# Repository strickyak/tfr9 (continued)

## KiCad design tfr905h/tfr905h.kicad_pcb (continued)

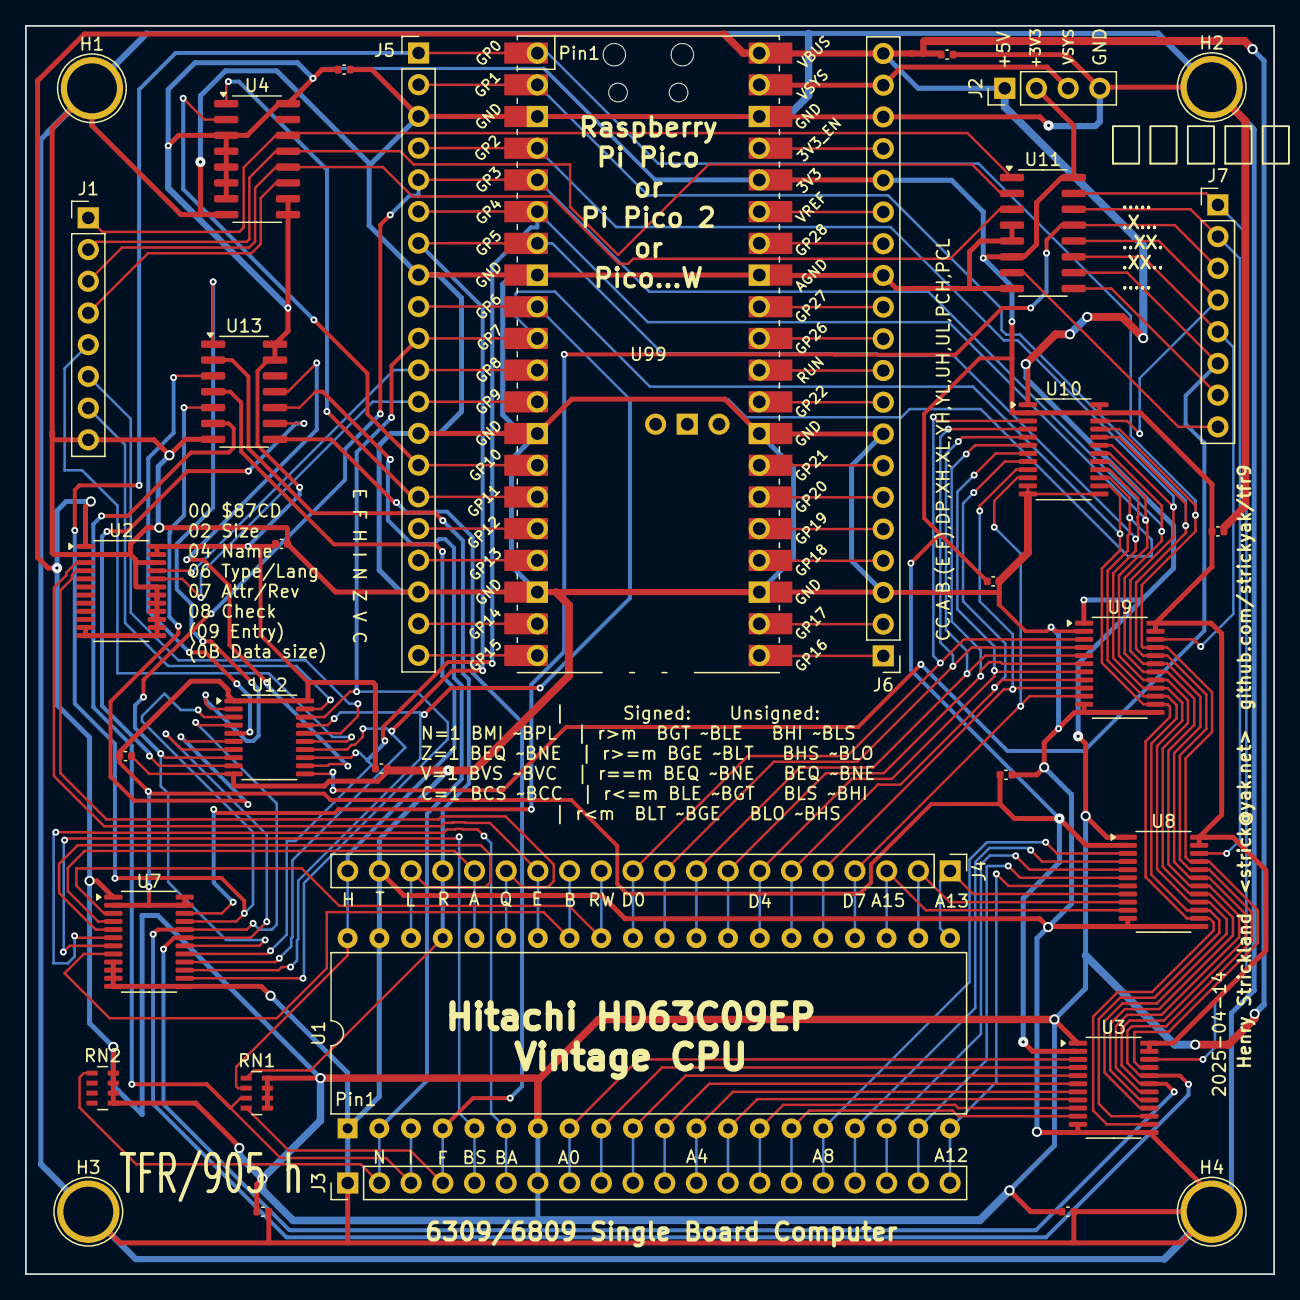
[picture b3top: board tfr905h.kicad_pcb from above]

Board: 2 copper layers, 100.0 x 100.0 mm, 35 parts (0 on the bottom side), 90 nets.

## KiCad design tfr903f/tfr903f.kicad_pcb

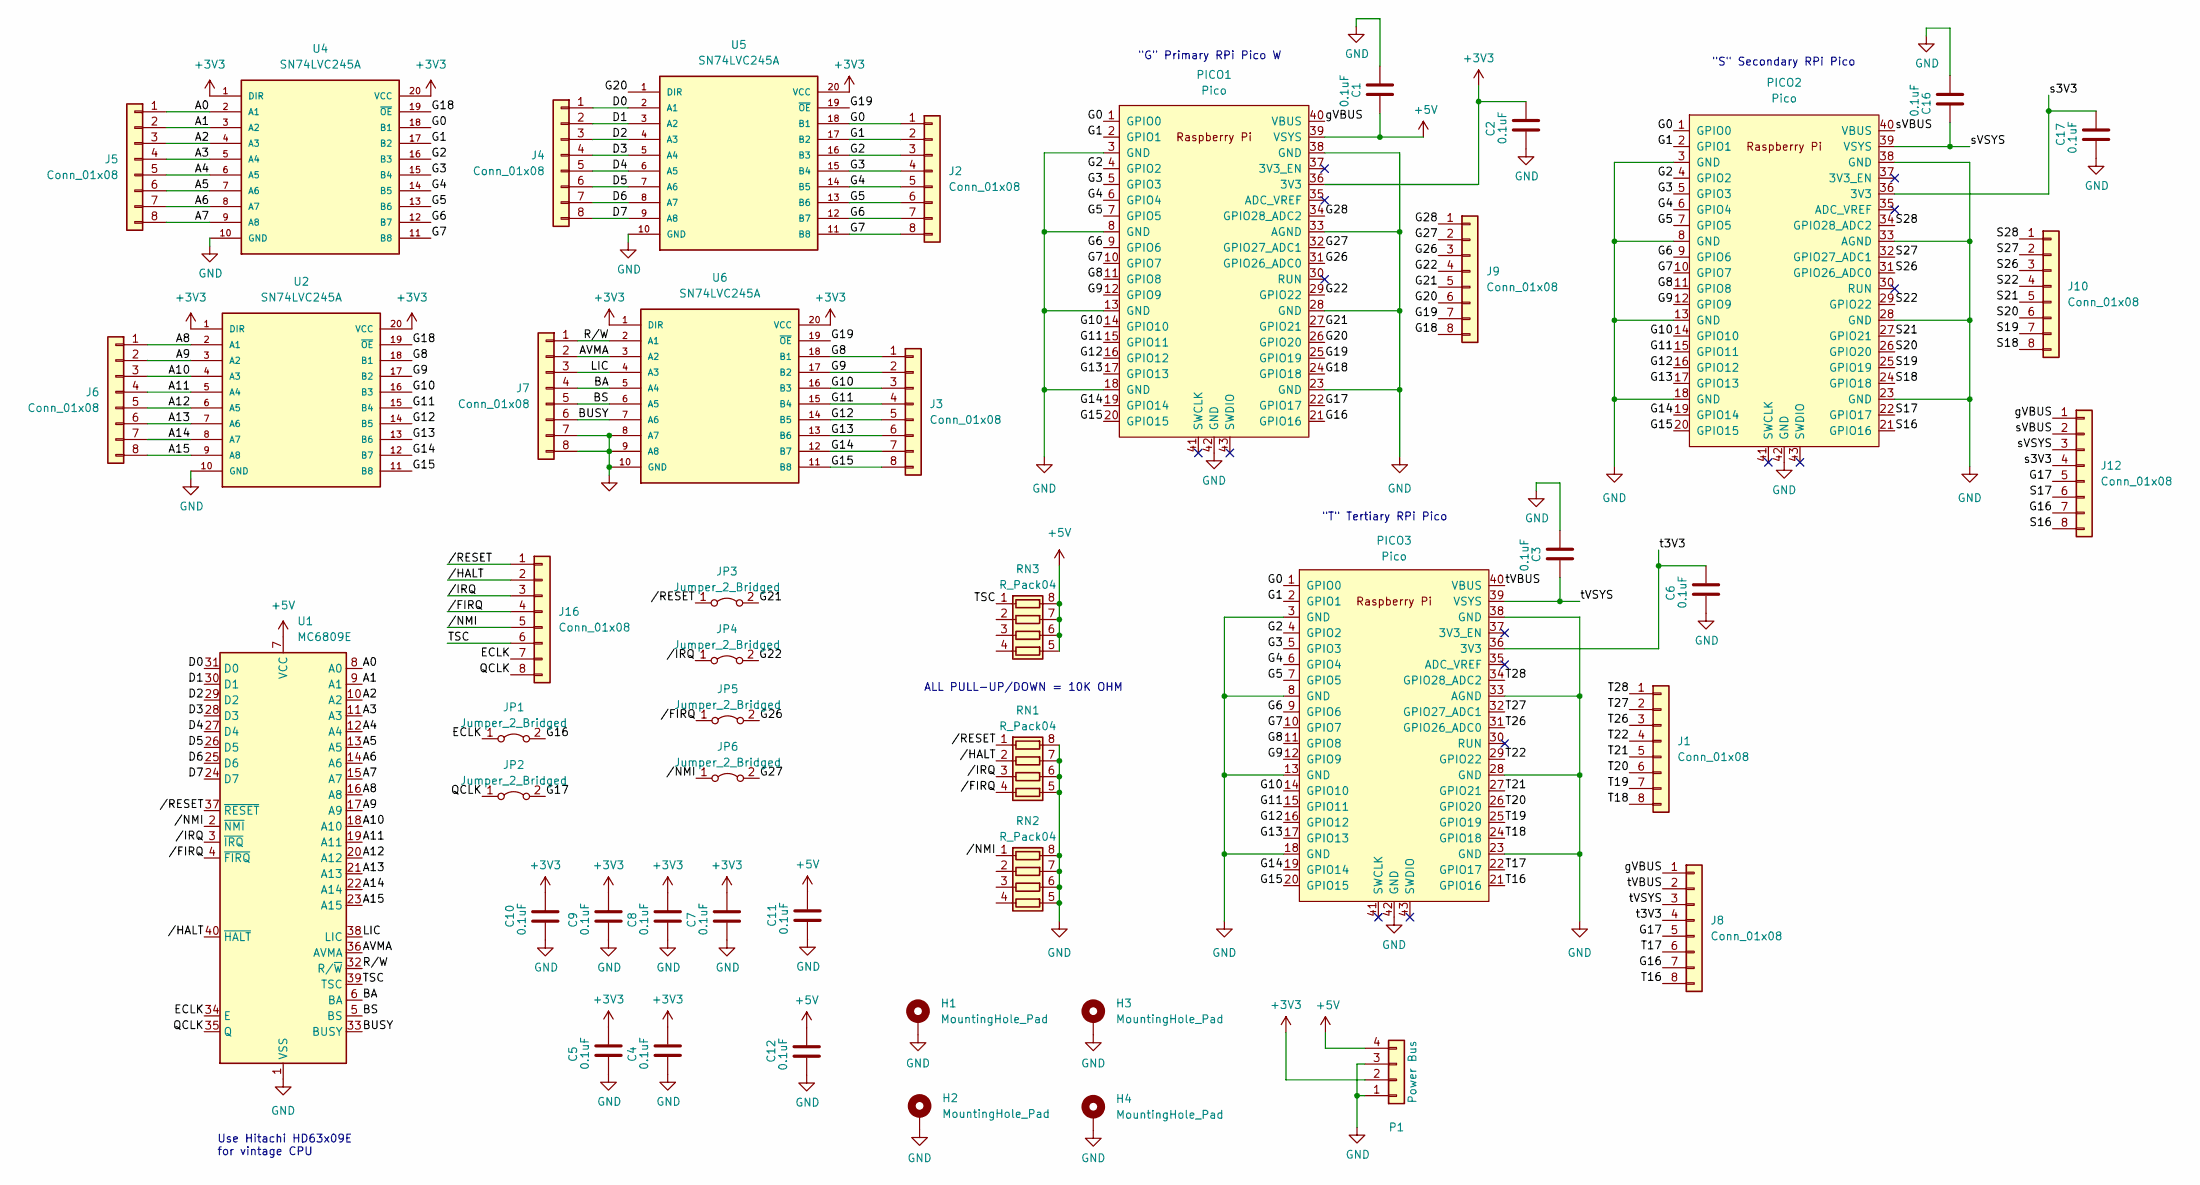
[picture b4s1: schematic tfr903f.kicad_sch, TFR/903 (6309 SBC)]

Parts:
C1, C2, C3, C4, C5, C6, C7, C8, C9, C10, C11, C12, C16, C17: 0.1uF; C_0402_1005Metric
H1, H2, H3, H4: MountingHole_Pad; TestPoint_Plated_Hole_D4.0mm
J1, J2, J3, J4, J5, J6, J7, J8, J9, J10, J12, J16: Conn_01x08; PinHeader_1x08_P2.54mm_Vertical
JP1, JP2, JP3, JP4, JP5, JP6: Jumper_2_Bridged; SolderJumper-2_P1.3mm_Bridged_Pad1.0x1.5mm
P1: Power Bus; PinHeader_1x04_P2.54mm_Vertical
PICO1, PICO2, PICO3: Pico; RPi_PicoW_SMD_TH
RN1, RN2, RN3: R_Pack04; R_Array_Concave_4x0603
U1: MC6809E; DIP-40_W15.24mm
U2, U4, U5, U6: SN74LVC245A; TSSOP-20_4.4x6.5mm_P0.65mm; MPN SN74LVC245AN

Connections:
+3V3: C2.1, C4.1, C5.1, C7.1, C8.1, C9.1, C10.1, P1.2, PICO1.36 (3V3), U2.1 (DIR), U2.20 (VCC), U4.1 (DIR), U4.20 (VCC), U5.20 (VCC), U6.1 (DIR), U6.20 (VCC)
+5V: C1.1, C11.1, C12.1, P1.4, PICO1.39 (VSYS), RN3.5 (R4.2), RN3.6 (R3.2), RN3.7 (R2.2), RN3.8 (R1.2), U1.7 (VCC)
/A0: J5.1, U1.8 (A0), U4.2 (A1)
/A1: J5.2, U1.9 (A1), U4.3 (A2)
/A2: J5.3, U1.10 (A2), U4.4 (A3)
/A3: J5.4, U1.11 (A3), U4.5 (A4)
/A4: J5.5, U1.12 (A4), U4.6 (A5)
/A5: J5.6, U1.13 (A5), U4.7 (A6)
/A6: J5.7, U1.14 (A6), U4.8 (A7)
/A7: J5.8, U1.15 (A7), U4.9 (A8)
/A8: J6.1, U1.16 (A8), U2.2 (A1)
/A9: J6.2, U1.17 (A9), U2.3 (A2)
/A10: J6.3, U1.18 (A10), U2.4 (A3)
/A11: J6.4, U1.19 (A11), U2.5 (A4)
/A12: J6.5, U1.20 (A12), U2.6 (A5)
/A13: J6.6, U1.21 (A13), U2.7 (A6)
/A14: J6.7, U1.22 (A14), U2.8 (A7)
/A15: J6.8, U1.23 (A15), U2.9 (A8)
/AVMA: J7.2, U1.36 (AVMA), U6.3 (A2)
/BA: J7.4, U1.6 (BA), U6.5 (A4)
/BS: J7.5, U1.5 (BS), U6.6 (A5)
/BUSY: J7.6, U1.33 (BUSY), U6.7 (A6)
/D0: J4.1, U1.31 (D0), U5.2 (A1)
/D1: J4.2, U1.30 (D1), U5.3 (A2)
/D2: J4.3, U1.29 (D2), U5.4 (A3)
/D3: J4.4, U1.28 (D3), U5.5 (A4)
/D4: J4.5, U1.27 (D4), U5.6 (A5)
/D5: J4.6, U1.26 (D5), U5.7 (A6)
/D6: J4.7, U1.25 (D6), U5.8 (A7)
/D7: J4.8, U1.24 (D7), U5.9 (A8)
/ECLK: J16.7, JP1.1 (A), U1.34 (E)
/G0: J2.1, PICO1.1 (GPIO0), PICO2.1 (GPIO0), PICO3.1 (GPIO0), U4.18 (B1), U5.18 (B1)
/G1: J2.2, PICO1.2 (GPIO1), PICO2.2 (GPIO1), PICO3.2 (GPIO1), U4.17 (B2), U5.17 (B2)
/G2: J2.3, PICO1.4 (GPIO2), PICO2.4 (GPIO2), PICO3.4 (GPIO2), U4.16 (B3), U5.16 (B3)
/G3: J2.4, PICO1.5 (GPIO3), PICO2.5 (GPIO3), PICO3.5 (GPIO3), U4.15 (B4), U5.15 (B4)
/G4: J2.5, PICO1.6 (GPIO4), PICO2.6 (GPIO4), PICO3.6 (GPIO4), U4.14 (B5), U5.14 (B5)
/G5: J2.6, PICO1.7 (GPIO5), PICO2.7 (GPIO5), PICO3.7 (GPIO5), U4.13 (B6), U5.13 (B6)
/G6: J2.7, PICO1.9 (GPIO6), PICO2.9 (GPIO6), PICO3.9 (GPIO6), U4.12 (B7), U5.12 (B7)
/G7: J2.8, PICO1.10 (GPIO7), PICO2.10 (GPIO7), PICO3.10 (GPIO7), U4.11 (B8), U5.11 (B8)
/G8: J3.1, PICO1.11 (GPIO8), PICO2.11 (GPIO8), PICO3.11 (GPIO8), U2.18 (B1), U6.18 (B1)
/G9: J3.2, PICO1.12 (GPIO9), PICO2.12 (GPIO9), PICO3.12 (GPIO9), U2.17 (B2), U6.17 (B2)
/G10: J3.3, PICO1.14 (GPIO10), PICO2.14 (GPIO10), PICO3.14 (GPIO10), U2.16 (B3), U6.16 (B3)
/G11: J3.4, PICO1.15 (GPIO11), PICO2.15 (GPIO11), PICO3.15 (GPIO11), U2.15 (B4), U6.15 (B4)
/G12: J3.5, PICO1.16 (GPIO12), PICO2.16 (GPIO12), PICO3.16 (GPIO12), U2.14 (B5), U6.14 (B5)
/G13: J3.6, PICO1.17 (GPIO13), PICO2.17 (GPIO13), PICO3.17 (GPIO13), U2.13 (B6), U6.13 (B6)
/G14: J3.7, PICO1.19 (GPIO14), PICO2.19 (GPIO14), PICO3.19 (GPIO14), U2.12 (B7), U6.12 (B7)
/G15: J3.8, PICO1.20 (GPIO15), PICO2.20 (GPIO15), PICO3.20 (GPIO15), U2.11 (B8), U6.11 (B8)
/G16: J8.7, J12.7, JP1.2 (B), PICO1.21 (GPIO16)
/G17: J8.5, J12.5, JP2.2 (B), PICO1.22 (GPIO17)
/G18: J9.8, PICO1.24 (GPIO18), U2.19 (~OE), U4.19 (~OE)
/G19: J9.7, PICO1.25 (GPIO19), U5.19 (~OE), U6.19 (~OE)
/G20: J9.6, PICO1.26 (GPIO20), U5.1 (DIR)
/G21: J9.5, JP3.2 (B), PICO1.27 (GPIO21)
/G22: J9.4, JP4.2 (B), PICO1.29 (GPIO22)
/G26: J9.3, JP5.2 (B), PICO1.31 (GPIO26_ADC0)
/G27: J9.2, JP6.2 (B), PICO1.32 (GPIO27_ADC1)
/G28: J9.1, PICO1.34 (GPIO28_ADC2)
/LIC: J7.3, U1.38 (LIC), U6.4 (A3)
/QCLK: J16.8, JP2.1 (A), U1.35 (Q)
/R/W: J7.1, U1.32 (R/~W), U6.2 (A1)
/S16: J12.8, PICO2.21 (GPIO16)
/S17: J12.6, PICO2.22 (GPIO17)
/S18: J10.8, PICO2.24 (GPIO18)
/S19: J10.7, PICO2.25 (GPIO19)
/S20: J10.6, PICO2.26 (GPIO20)
/S21: J10.5, PICO2.27 (GPIO21)
/S22: J10.4, PICO2.29 (GPIO22)
/S26: J10.3, PICO2.31 (GPIO26_ADC0)
/S27: J10.2, PICO2.32 (GPIO27_ADC1)
/S28: J10.1, PICO2.34 (GPIO28_ADC2)
/T16: J8.8, PICO3.21 (GPIO16)
/T17: J8.6, PICO3.22 (GPIO17)
/T18: J1.8, PICO3.24 (GPIO18)
/T19: J1.7, PICO3.25 (GPIO19)
/T20: J1.6, PICO3.26 (GPIO20)
/T21: J1.5, PICO3.27 (GPIO21)
/T22: J1.4, PICO3.29 (GPIO22)
/T26: J1.3, PICO3.31 (GPIO26_ADC0)
/T27: J1.2, PICO3.32 (GPIO27_ADC1)
/T28: J1.1, PICO3.34 (GPIO28_ADC2)
/TSC: J16.6, RN3.1 (R1.1), U1.39 (TSC)
/gVBUS: J8.1, J12.1, PICO1.40 (VBUS)
/s3V3: C17.1, J12.4, PICO2.36 (3V3)
/sVBUS: J12.2, PICO2.40 (VBUS)
/sVSYS: C16.1, J12.3, PICO2.39 (VSYS)
/t3V3: C6.1, J8.4, PICO3.36 (3V3)
/tVBUS: J8.2, PICO3.40 (VBUS)
/tVSYS: C3.1, J8.3, PICO3.39 (VSYS)
//FIRQ: J16.4, JP5.1 (A), RN1.4 (R4.1), U1.4 (~FIRQ)
//HALT: J16.2, RN1.2 (R2.1), U1.40 (~HALT)
//IRQ: J16.3, JP4.1 (A), RN1.3 (R3.1), U1.3 (~IRQ)
//NMI: J16.5, JP6.1 (A), RN2.1 (R1.1), U1.2 (~NMI)
//RESET: J16.1, JP3.1 (A), RN1.1 (R1.1), U1.37 (~RESET)
GND: C1.2, C2.2, C3.2, C4.2, C5.2, C6.2, C7.2, C8.2, C9.2, C10.2, C11.2, C12.2, C16.2, C17.2, H1.1, H2.1, H3.1, H4.1, J7.7, J7.8, P1.1, P1.3, PICO1.3 (GND), PICO1.8 (GND), PICO1.13 (GND), PICO1.18 (GND), PICO1.23 (GND), PICO1.28 (GND), PICO1.33 (AGND), PICO1.38 (GND), PICO1.42 (GND), PICO2.3 (GND), PICO2.8 (GND), PICO2.13 (GND), PICO2.18 (GND), PICO2.23 (GND), PICO2.28 (GND), PICO2.33 (AGND), PICO2.38 (GND), PICO2.42 (GND), PICO3.3 (GND), PICO3.8 (GND), PICO3.13 (GND), PICO3.18 (GND), PICO3.23 (GND), PICO3.28 (GND), PICO3.33 (AGND), PICO3.38 (GND), PICO3.42 (GND), RN1.5 (R4.2), RN1.6 (R3.2), RN1.7 (R2.2), RN1.8 (R1.2), RN2.5 (R4.2), RN2.6 (R3.2), RN2.7 (R2.2), RN2.8 (R1.2), U1.1 (VSS), U2.10 (GND), U4.10 (GND), U5.10 (GND), U6.8 (A7), U6.9 (A8), U6.10 (GND)

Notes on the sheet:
"G" Primary RPi Pico W
"T" Tertiary RPi Pico
"S" Secondary RPi Pico
ALL PULL-UP/DOWN = 10K OHM
Use Hitachi HD63x09E for vintage CPU

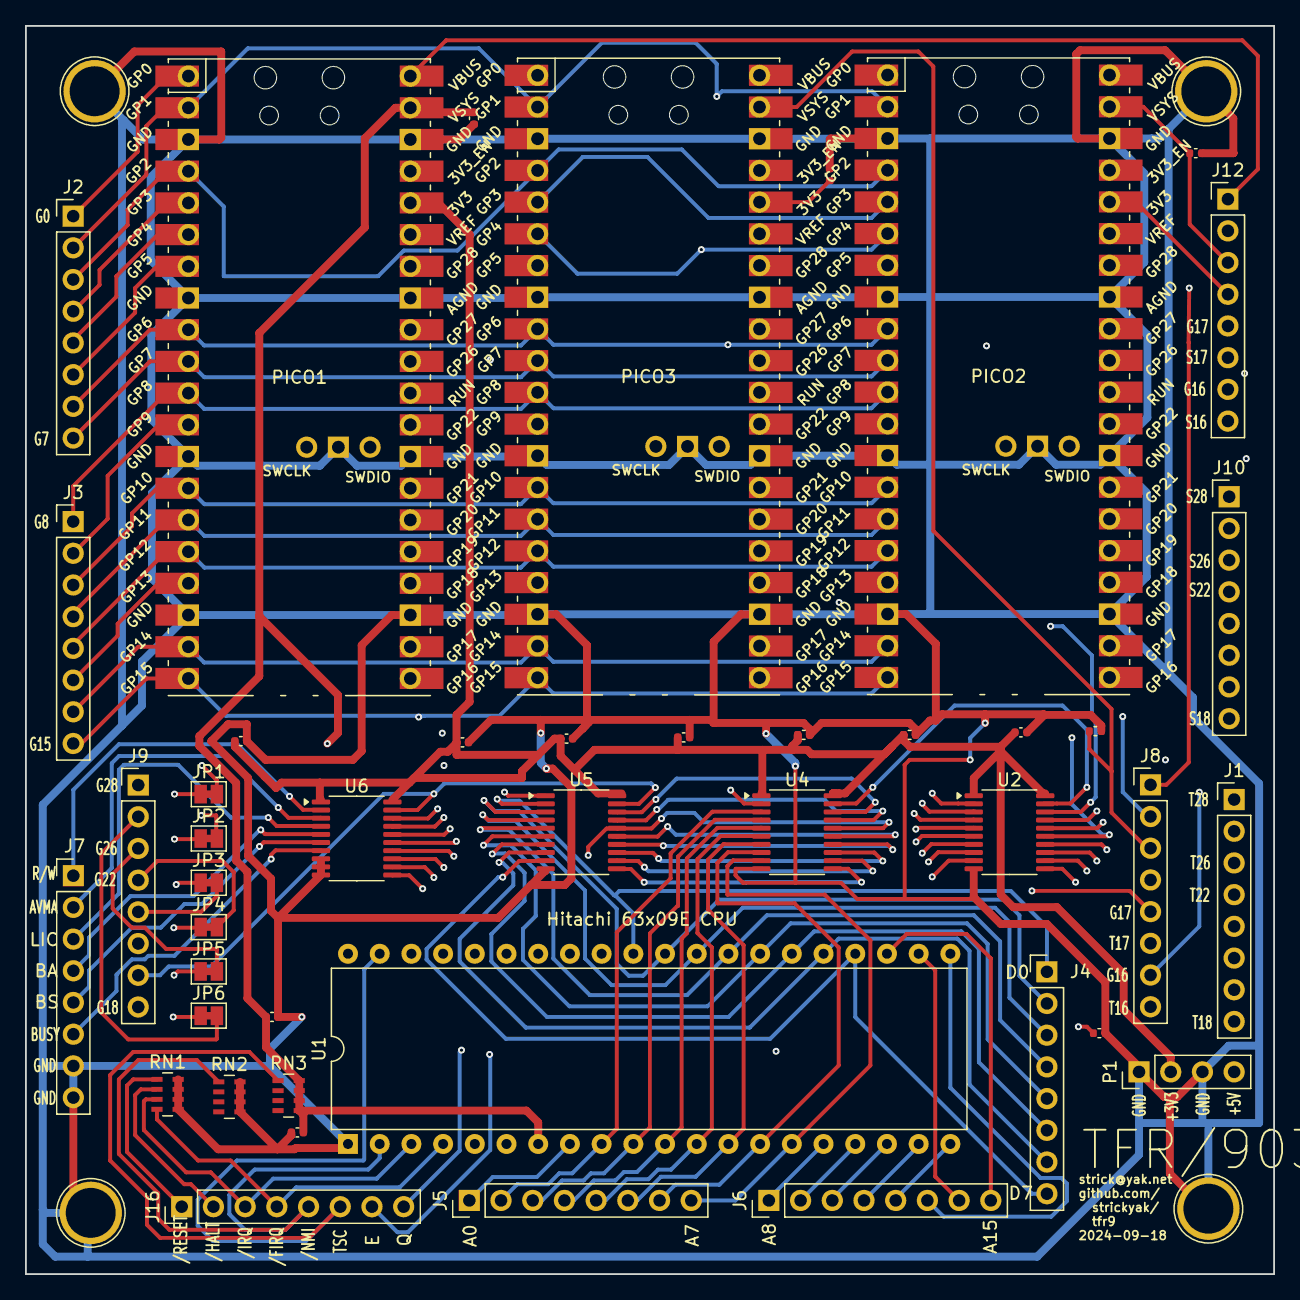
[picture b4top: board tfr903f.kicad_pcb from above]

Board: 4 copper layers, 100.0 x 100.0 mm, 48 parts (0 on the bottom side), 94 nets.

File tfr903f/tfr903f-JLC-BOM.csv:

Id,Designator,Footprint,Quantity,Designation,Supplier and ref,JLC,LCSC
1,"C6,C9,C1,C17,C2,C4,C8,C3,C11,C7,C5,C16,C12,C10",C_0402_1005Metric,14,16V 100nF X7R ±10% 0402 Multilayer Ceramic Capacitors MLCC - SMD/SMT ROHS,CL05B104KO5NNNC,402,C1525
3,"RN2,RN3,RN1",R_Array_Concave_4x0603,3,"4 ±5% 10kΩ 62.5mW ±200ppm/℃ 0603x4 Resistor Networks, Arrays ROHS",4D03WGJ0103T5E,0603x4,C29718
6,"U6,U5,U2,U4",TSSOP-20_4.4x6.5mm_P0.65mm,4,SN74LVC245A Logic Gate,C7494910,TSSOP-20,C7494910
9,U1,DIP-40_W15.24mm,1,40P DIP 15.24mm 2.54mm DIP-40 IC / Transistor Socket ROHS,IC-40P,DIP-40,C2332
41,PICO1,RPi_PicoW_SMD_TH,1,Raspberry Pi Pico W,Raspberry Pi,Pico W,C7203003
42,"PICO3,PICO2",RPi_PicoW_SMD_TH,2,Raspberry Pi Pico,Raspberry Pi,Pico,C7203002

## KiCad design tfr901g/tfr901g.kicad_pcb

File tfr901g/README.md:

# CoPiCo PCB KiCad Files

The CoPiCo is a cartridge for the Tandy Color Computer that adds WiFi to and
serves as a boot ROM for the system. It is based on the Raspberry Pi Pico W
microcontroller dev board, which includes onboard WiFi.

[copico_rev0.2_schematic_v0.2.9.pdf](assets/copico_rev0.2_schematic_v0.2.9.pdf)

## WiFi Connectivity

The firmware (see 'copico-firmware' repo) will behave more like a SPI WiFi
module or the WizNet chip (or perhaps both, depending on mode). It will, of
course, also allow listing and connecting to the desired WiFi network.

## ROM Emulation

CoPiCo will also support boot ROM emulation (initially just for a 1 KB ROM due
to limitations of first revision of the CoPiCo PCB). Henry Strickland
(@strickyak) plans to use this feature to load a version of his
"axiom" network boot ROM (see
https://github.com/strickyak/frobio/tree/main/frob3/booting).

## Other Future Capabilities

Future capabilities for the CoPiCo may include:
- VGA or HDMI output based on the captured contents of video RAM
- Logic capture / bus trace
- Remote debug, with breakpoints and watchpoints

## Stay Tuned to This Channel

Please star this repo and/or watch this space for updates as development
continues!

Thank you for being a part of the Retrocomputing community!

Thomas Shanks (copico@tshanks.org)

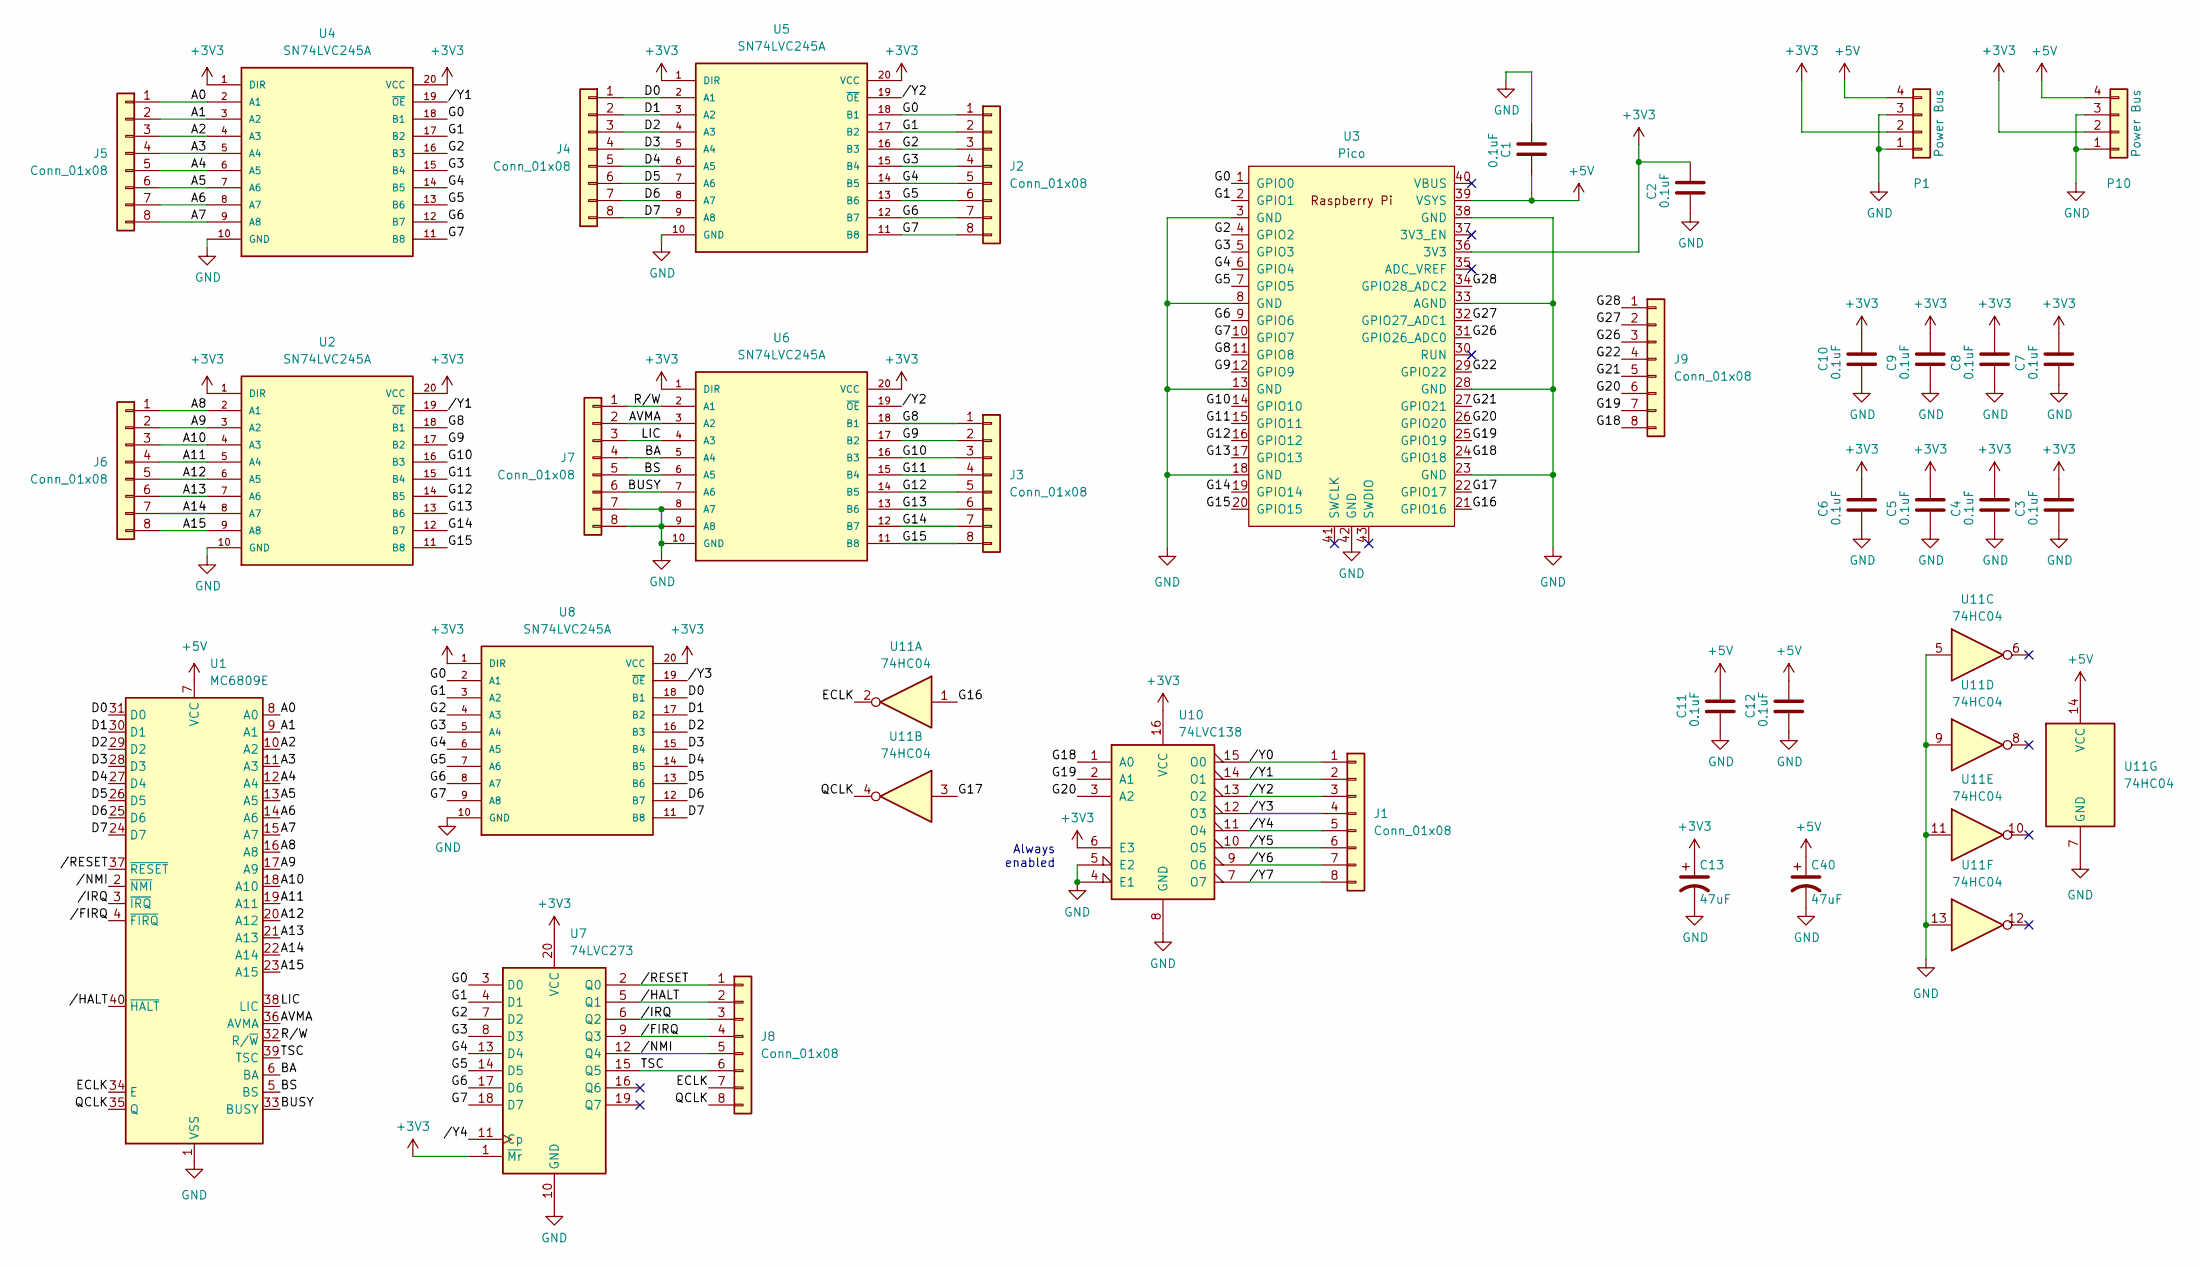
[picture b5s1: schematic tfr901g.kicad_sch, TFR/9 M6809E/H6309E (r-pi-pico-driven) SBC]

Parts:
C1, C2, C3, C4, C5, C6, C7, C8, C9, C10, C11, C12: 0.1uF; C_Disc_D5.0mm_W2.5mm_P5.00mm
C13, C40: 47uF; CP_Radial_D7.5mm_P2.50mm
J1, J2, J3, J4, J5, J6, J7, J8, J9: Conn_01x08; PinHeader_1x08_P2.54mm_Vertical
P1, P10: Power Bus; PinHeader_1x04_P2.54mm_Vertical
U1: MC6809E; DIP-40_W15.24mm
U2, U4, U5, U6, U8: SN74LVC245A; DIP20-2.54-26.2X7.62MM; MPN SN74LVC245AN
U3: Pico; RPi_PicoW_SMD_TH
U7: 74LVC273; DIP-20_W7.62mm_Socket
U10: 74LVC138; DIP-16_W7.62mm_Socket
U11: 74HC04; DIP-14_W7.62mm_Socket

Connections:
+3V3: C2.1, C3.1, C4.1, C5.1, C6.1, C7.1, C8.1, C9.1, C10.1, C13.1, P1.2, P10.2, U2.1 (DIR), U2.20 (VCC), U3.36 (3V3), U4.1 (DIR), U4.20 (VCC), U5.1 (DIR), U5.20 (VCC), U6.1 (DIR), U6.20 (VCC), U7.1 (~Mr), U7.20 (VCC), U8.1 (DIR), U8.20 (VCC), U10.6 (E3), U10.16 (VCC)
+5V: C1.1, C11.1, C12.1, C40.1, P1.4, P10.4, U1.7 (VCC), U3.39 (VSYS), U11.14 (VCC)
/A0: J5.1, U1.8 (A0), U4.2 (A1)
/A1: J5.2, U1.9 (A1), U4.3 (A2)
/A2: J5.3, U1.10 (A2), U4.4 (A3)
/A3: J5.4, U1.11 (A3), U4.5 (A4)
/A4: J5.5, U1.12 (A4), U4.6 (A5)
/A5: J5.6, U1.13 (A5), U4.7 (A6)
/A6: J5.7, U1.14 (A6), U4.8 (A7)
/A7: J5.8, U1.15 (A7), U4.9 (A8)
/A8: J6.1, U1.16 (A8), U2.2 (A1)
/A9: J6.2, U1.17 (A9), U2.3 (A2)
/A10: J6.3, U1.18 (A10), U2.4 (A3)
/A11: J6.4, U1.19 (A11), U2.5 (A4)
/A12: J6.5, U1.20 (A12), U2.6 (A5)
/A13: J6.6, U1.21 (A13), U2.7 (A6)
/A14: J6.7, U1.22 (A14), U2.8 (A7)
/A15: J6.8, U1.23 (A15), U2.9 (A8)
/AVMA: J7.2, U1.36 (AVMA), U6.3 (A2)
/BA: J7.4, U1.6 (BA), U6.5 (A4)
/BS: J7.5, U1.5 (BS), U6.6 (A5)
/BUSY: J7.6, U1.33 (BUSY), U6.7 (A6)
/D0: J4.1, U1.31 (D0), U5.2 (A1), U8.18 (B1)
/D1: J4.2, U1.30 (D1), U5.3 (A2), U8.17 (B2)
/D2: J4.3, U1.29 (D2), U5.4 (A3), U8.16 (B3)
/D3: J4.4, U1.28 (D3), U5.5 (A4), U8.15 (B4)
/D4: J4.5, U1.27 (D4), U5.6 (A5), U8.14 (B5)
/D5: J4.6, U1.26 (D5), U5.7 (A6), U8.13 (B6)
/D6: J4.7, U1.25 (D6), U5.8 (A7), U8.12 (B7)
/D7: J4.8, U1.24 (D7), U5.9 (A8), U8.11 (B8)
/ECLK: J8.7, U1.34 (E), U11.2
/G0: J2.1, U3.1 (GPIO0), U4.18 (B1), U5.18 (B1), U7.3 (D0), U8.2 (A1)
/G1: J2.2, U3.2 (GPIO1), U4.17 (B2), U5.17 (B2), U7.4 (D1), U8.3 (A2)
/G2: J2.3, U3.4 (GPIO2), U4.16 (B3), U5.16 (B3), U7.7 (D2), U8.4 (A3)
/G3: J2.4, U3.5 (GPIO3), U4.15 (B4), U5.15 (B4), U7.8 (D3), U8.5 (A4)
/G4: J2.5, U3.6 (GPIO4), U4.14 (B5), U5.14 (B5), U7.13 (D4), U8.6 (A5)
/G5: J2.6, U3.7 (GPIO5), U4.13 (B6), U5.13 (B6), U7.14 (D5), U8.7 (A6)
/G6: J2.7, U3.9 (GPIO6), U4.12 (B7), U5.12 (B7), U7.17 (D6), U8.8 (A7)
/G7: J2.8, U3.10 (GPIO7), U4.11 (B8), U5.11 (B8), U7.18 (D7), U8.9 (A8)
/G8: J3.1, U2.18 (B1), U3.11 (GPIO8), U6.18 (B1)
/G9: J3.2, U2.17 (B2), U3.12 (GPIO9), U6.17 (B2)
/G10: J3.3, U2.16 (B3), U3.14 (GPIO10), U6.16 (B3)
/G11: J3.4, U2.15 (B4), U3.15 (GPIO11), U6.15 (B4)
/G12: J3.5, U2.14 (B5), U3.16 (GPIO12), U6.14 (B5)
/G13: J3.6, U2.13 (B6), U3.17 (GPIO13), U6.13 (B6)
/G14: J3.7, U2.12 (B7), U3.19 (GPIO14), U6.12 (B7)
/G15: J3.8, U2.11 (B8), U3.20 (GPIO15), U6.11 (B8)
/G16: U3.21 (GPIO16), U11.1
/G17: U3.22 (GPIO17), U11.3
/G18: J9.8, U3.24 (GPIO18), U10.1 (A0)
/G19: J9.7, U3.25 (GPIO19), U10.2 (A1)
/G20: J9.6, U3.26 (GPIO20), U10.3 (A2)
/G21: J9.5, U3.27 (GPIO21)
/G22: J9.4, U3.29 (GPIO22)
/G26: J9.3, U3.31 (GPIO26_ADC0)
/G27: J9.2, U3.32 (GPIO27_ADC1)
/G28: J9.1, U3.34 (GPIO28_ADC2)
/LIC: J7.3, U1.38 (LIC), U6.4 (A3)
/QCLK: J8.8, U1.35 (Q), U11.4
/R/W: J7.1, U1.32 (R/~W), U6.2 (A1)
/TSC: J8.6, U1.39 (TSC), U7.15 (Q5)
//FIRQ: J8.4, U1.4 (~FIRQ), U7.9 (Q3)
//HALT: J8.2, U1.40 (~HALT), U7.5 (Q1)
//IRQ: J8.3, U1.3 (~IRQ), U7.6 (Q2)
//NMI: J8.5, U1.2 (~NMI), U7.12 (Q4)
//RESET: J8.1, U1.37 (~RESET), U7.2 (Q0)
//Y0: J1.1, U10.15 (O0)
//Y1: J1.2, U2.19 (~OE), U4.19 (~OE), U10.14 (O1)
//Y2: J1.3, U5.19 (~OE), U6.19 (~OE), U10.13 (O2)
//Y3: J1.4, U8.19 (~OE), U10.12 (O3)
//Y4: J1.5, U7.11 (Cp), U10.11 (O4)
//Y5: J1.6, U10.10 (O5)
//Y6: J1.7, U10.9 (O6)
//Y7: J1.8, U10.7 (O7)
GND: C1.2, C2.2, C3.2, C4.2, C5.2, C6.2, C7.2, C8.2, C9.2, C10.2, C11.2, C12.2, C13.2, C40.2, J7.7, J7.8, P1.1, P1.3, P10.1, P10.3, U1.1 (VSS), U2.10 (GND), U3.3 (GND), U3.8 (GND), U3.13 (GND), U3.18 (GND), U3.23 (GND), U3.28 (GND), U3.33 (AGND), U3.38 (GND), U3.42 (GND), U4.10 (GND), U5.10 (GND), U6.8 (A7), U6.9 (A8), U6.10 (GND), U7.10 (GND), U8.10 (GND), U10.4 (E1), U10.5 (E2), U10.8 (GND), U11.5, U11.7 (GND), U11.9, U11.11, U11.13

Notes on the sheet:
Always enabled

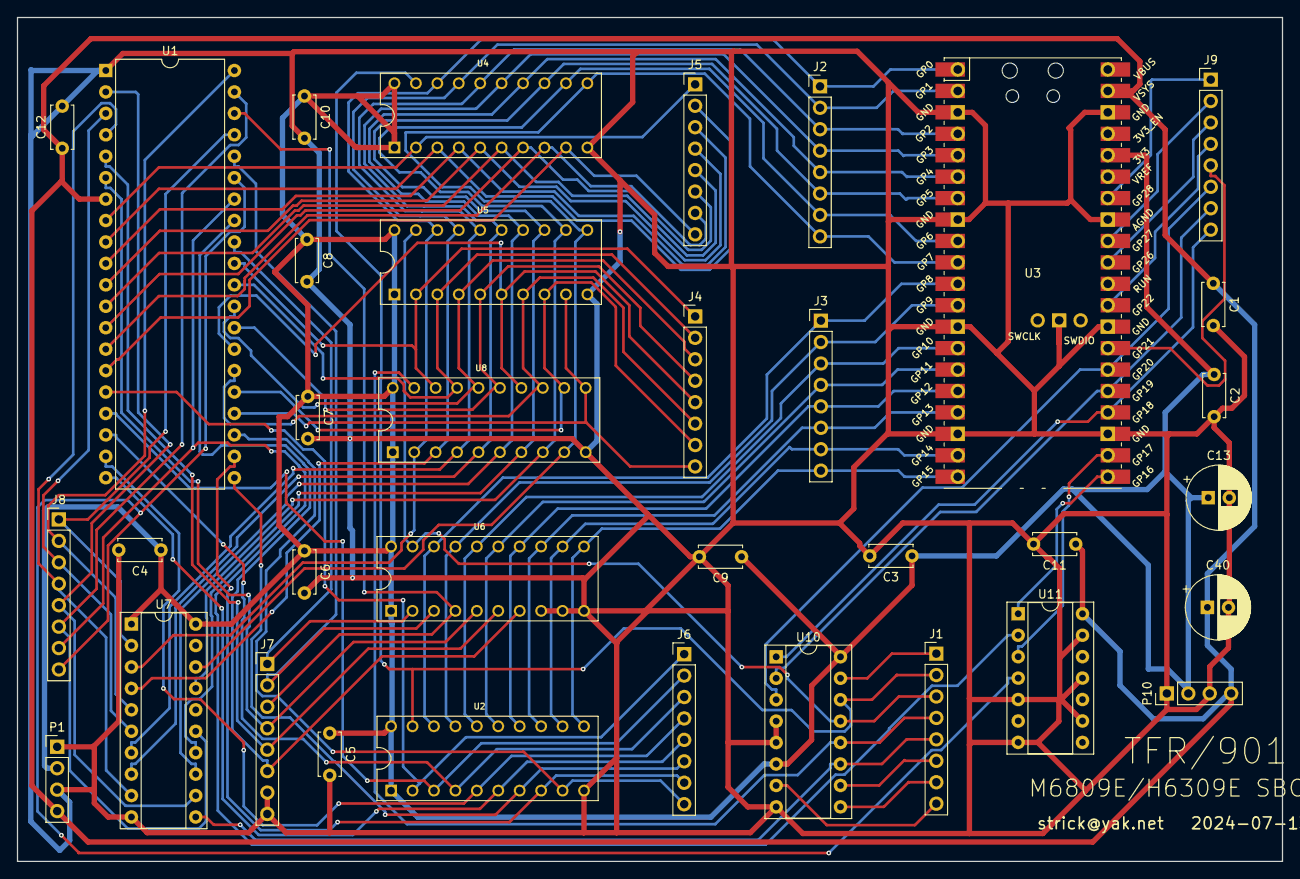
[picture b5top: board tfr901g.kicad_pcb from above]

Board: 2 copper layers, 149.9 x 100.0 mm, 35 parts (0 on the bottom side), 75 nets.

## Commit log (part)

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2026-01-22 Sstart adding Unit CardKb v1.1
2026-01-23 cyberterm: ssd1306 and cardkb
2026-01-25 cyberterm.h
2026-01-28 FuzixScriptWIP.sh
2026-01-28 typo in tconsole/ram_coco3.go, j not i
2026-01-28 tmanager905/tmanager.h for Fuzix
2026-01-29 add coco2-vectors.0xfff0.rom coco2-vectors-6309.0xfff0.rom
2026-01-31 coco2 with c/1 and websocket
2026-01-31 PMODE1 works in web server
2026-02-12 added PMODE 4.
2026-02-12 Pmode 1 & 4, but need work on 2 and 3 and colorset
2026-02-12 add the vendored websocket library
2026-02-12 fix inverted chars to full 12 tall
2026-02-12 typo in index var caused panic
2026-02-12 vector ROM files for coco3
2026-02-18 for centipede0
2026-03-07 tconsole/disk.go fixes
2026-03-16 3-byte (2 addr 1 data) read & write cycle logging
2026-03-20 flag --centipede for tconsole.go
2026-03-21 make double sided work, with "--disks=d0:/tmp/foo.dsk"
2026-03-21 useful disasm of grab read of centipede level1
2026-03-21 oops, Os9Level1.MemoryModuleOf was being used by centipede
2026-03-21 making disk.go work with boot floppy level1 coco2
2026-03-21 before discovering CONTROL after COMMAND for dden
2026-04-04 fix for /bin/sh on 32bit r pi os that has no time
2026-04-04 trying out, didn't work: export picotool_DIR
2026-04-04 there is no `rfs1` yet
2026-04-04 printable C_CYCLE
2026-04-06 make tfr9 L1 & L2 work again
2026-04-07 fix final byte of sector, esp reading sectors (was always 0xFC).
2026-04-13 samvdg inversion of text mode
2026-05-13 Initial testing -- tmanager911 for TFR/911H
2026-05-13 TFR/911H kicad files
2026-06-01 attempting tfr9/v3/tmanager911/very-fast (JSR works)
2026-06-01 playing with DIVISOR
2026-06-02 tfr911: rate=3.677614e+06,div=1,8x6,gc_ok
2026-06-02 very-fast 4.693MHz with fewer checks
2026-06-04 use label for both 905 and future 911 (untested)
2026-06-08 white space
2026-06-08 tfr9/v3/tmanager911/very-turbos works: 3.6-4.0MHz
